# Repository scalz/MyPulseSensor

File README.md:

# MyMultisensors

This is a simple, cheap and low power sensor which can be used, for example, with your favorite battery powered node, for counting power meters blinking led pulses. 

I've decided to not use the well known LM393 module with photodiode because the combo has some power consumption (0.4mA for the comparator only + rest of the circuit, even if no pulses). 

I also thought there is not always the possibility to have an external power supply, when power counters are outdoor for instance.
But sure, the advantage to use a comparator is we get a nice digital voltage level for the signal to the node.

So I got the idea to use a mosfet with a photoresistor and just a few resistors, which i think should be enough :) 

Lot of docs about photoresistors on the internet, but quickly, the photoresistor operation is very simple, and allow us to be low power though: 
- In darkness, in datasheet you can see it's rated for 200k to >1M, in practice, in darkness (i've checked mine), it's in >1Mohms range.
- In light conditions, it falls to 20k for instance.

And i've used it like this :
- the P-mosfet is enabled when the photoresistor is pulled down, detecting a pulse (remember approx 20k, depends on the light intensity). The Source pin of the mosfet being VCC , this is what we get on its Drain pin which is also the Led indicator and Signal pin of the module
- when there is no pulses, the photores is >1M, and we get "1" logic level to the gate of the P-mosfet. So, nothing on signal pin.

The pros:
- the way the mosfet is connected allows a good reliable voltage level for the PULSE signal pin 
- we can also expect a good voltage range of operation, for battery powered device this may be useful
- the resistors combined with the photoresistor consumes just a very few uA depending on their values

I've quickly tested it with a signal generator and was able to detect up to 100Hz. Which should be enough for lot of power meters i think..
An example, for 50Hz frequency blinking led :
- 50 pulses/sec so 50*3600 pulses/hour gives us 180000 pulses/hour
- says at this rate, you're consuming 20kw/h, wow! Then we would get 9000 pulses/kw on the power meter side..

I've done two pcb versions that you can order here in case you want to play with it:
- SMD for those like me who're fond of this.. : https://PCBs.io/share/z5bXQ
- Through hole for those who are thinking i'm boring with my SMD : https://PCBs.io/share/zvVP1

**SMD version**

**Through hole version**

**PCB**

**Assembled, Top led view**

**Assembled, Bottom photoresistor view**

## General specs
------

PCB Size : diam. 18mm

**Schematic**

###### Pinout

- VCC : Connect to VCC of your board
- GND : Connect to GND
- PULSE : Connect to an IRQ pin on your board

An SMD Jumper is also available. Shunt it by soldering, if you need the led indicator (will use a bit more power, tweak the resistor|

To use the board, that's easy:
- Follow the above pinout
- If you add the optional onboard led, that will consumes more power of course. Tweak its resistor, or you can disable it thx to the jumper.
- Of course, you need the sensor well aligned in front of the blinking led. The main goal is to have a good dark/light detection.

I don't really need it, or maybe in future, because where I live there are others alternatives like a grid protocol providing lots of informations, but that was quick and fun to do!

Enjoy :)

## Known issues
------ 

## Donations
------

I'm trying to make opensource projects. I do this for free and sharing spirit. I don't do ads etc..
But if you think information here is worth of some money, or want to reward me, feel free to send any amount through paypal.

Or you can also order pcb here :
I will earn a little percentage that will allow me to order proto pcb and share more fun design.

Or pay me a protein smoothie if you see me! oh well, a beer is ok too :)

### Contributors
------
Always special thanks to:
- Mysensors Team for its great work

## Links, reference and license
------
- https://www.openhardware.io/view/352/MyPulse-Sensor

Copyright Scalz (2017). released under the CERN Open Hardware Licence v1.2

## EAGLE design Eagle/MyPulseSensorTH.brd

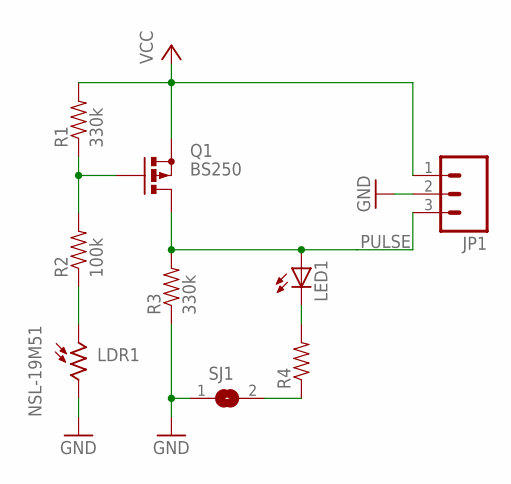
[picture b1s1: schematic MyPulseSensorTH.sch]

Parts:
JP1: M03PTH; 1X03
LDR1: NSL-19M51; PHOTORESISTOR_TO18
LED1: LED5MM
Q1: BS250; SOT54E
R1, R3: 330k; RESISTOR_TH
R2: 100k; RESISTOR_TH
R4: RESISTOR; RESISTOR_TH
SJ1: SJ

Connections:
GND: JP1.2, LDR1.2, R3.1, SJ1.1
unnamed: Q1.G, R1.1, R2.2
unnamed: LDR1.1, R2.1
unnamed: LED1.K (C), R4.2
unnamed: R4.1, SJ1.2
PULSE: JP1.3, LED1.A, Q1.D, R3.2
VCC: JP1.1, Q1.S, R1.2

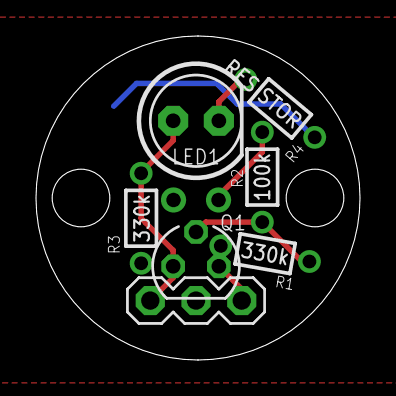
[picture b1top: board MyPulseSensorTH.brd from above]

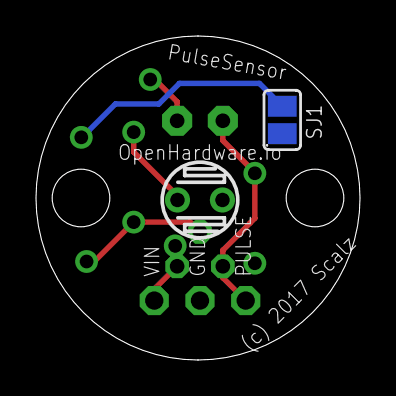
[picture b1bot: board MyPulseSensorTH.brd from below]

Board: 2 copper layers, 18.0 x 18.0 mm, 9 parts (2 on the bottom side), 7 nets.

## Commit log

2017-04-04 upload project files
2017-04-04 readme update

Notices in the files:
Eagle/MyPulseSensorTH.brd:
(c) 2017 Scalz
parts and their libraries:
SparkFun-Connectors: Licensing: Creative Commons ShareAlike 4.0 International - https://creativecommons.org/licenses/by-sa/4.0
